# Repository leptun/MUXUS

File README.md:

# MUXUS
This repository contains the MUXUS project, a USB 2.0 switch with 4 inputs (3xB + 1C_PD) and 4 outputs (3xA + STM32)

The project is split into multiple logical parts, all interconected on a PCB.
1. Upstream USB ports
2. USB mux
3. USB hub
4. Downstream USB ports
5. STM32 microcontroller
6. USB PD sink
7. STM32 programming
8. 3.3V rail Buck converter

## 1. Upstream USB ports
There are 4 upstream capable USB ports (UFP1-UFP4): 3x USB-B and 1xUSB-C

The USB-B ports (UFP2-4) are protected by `USBLC6-2SC6` ICs (VBUS, D+/-).

The USB-C port (UFP1) is protected by a `USBLC6-4SC6` IC (VBUS, D+/-, CC1/2).

## 2. USB mux
All Upstream facing ports (UFP) are connected to the USB mux IC (`TS3USBCA420RSVR`).
The mux output is connected to an internal usb bus called IFP (inner facing port).
Even though this IC is designed to multiplex SBU pins on USB-C ports, its bandwidth is high enough for USB 2.0 signals.
This IC is connected to the MCU via a 400KHz I2C bus. All control is done via I2C.

## 3. USB hub
The IFP bus is split into multiple downstream ports (DFP1-DFP4) using a USB 2.0 HS hub (`USB2504A-JT`).
The hub has an I2C interface as well and it is connected to the MCU via the same 400KHz I2C bus.
Most of the control is done via the I2C bus, but there are also a few extra pins required:
- HUB_RESET. It is an active low signal with an external pull-up resistor. It is needed because the I2C bus gets disabled by the hub when the Attach command is executed by the hub.
- IFP_VBUS. The MCU emulates the VBUS connection of the upstream ports since the MUX IC doesn't do that on its own.

Each DFP has a pair of status LEDs (green and amber):
- The green LED indicates if the device is connected and powered. It turns off when the device is suspended or when it is disconnected.
- The amber LED indicates a fault in the port. This seems to only happen when the VBUS is shorted to GND.

## 4. Downstream USB ports
There are 4 downstream capable ports (DFP1-4), however only 3 have connectors (DFP2-4).

DFP1 is connected directly to the mcu and, as a result, no power circuitry is required for this one.

DFP2-4 are usb-A ports. Each port is protected by `USBLC6-2SC6` ICs (VBUS, D+/-) and VBUS is switched using `AP2151W` ICs.

## 5. STM32 microcontroller
The MCU is a `STM32G441KBU6`.
There are a few reasons why this mcu was chosen, but the main restriction that made me choose this was the IC shortage.

The requirements for the mcu were as follows:
- Enough pins for controlling the board. A QFN32 IC was barely enough for this task. A 48 pin IC would have been much easier to use.
- 4 ADC inputs
- An I2C bus
- USB C PD capabilities
- Some kind of debug interface

Even though these requirements could have been fulfilled by much simpler MCUs, I chose this one as I wanted to learn how to use this MCU family.

## 6. USB PD sink
I wanted this hub to be fully featured, so I made sure that all downstream ports are capable of delivering the full USB 2.0 power specification.
As a result, 1.5A + whatever else consumes power on the board is required. The only method I could achieve this is by either using an external 5V power supply, or by using a USBC-PD capable charger. I chose the latter.
With USBC-PD, the board can communicate with the charger directly and request up to 3A at 5V. I configured it to only request 2A.
The UCPD stack provided by ST is surprisingly heavy, eating up ~70KB of flash. Luckily, it leaves enough flash for the rest of the code.

# 7. STM32 programming
The MCU can be programmed in multiple ways:
- The STDC14 connector is the main method I used. It has a SWD interface, SWO trace support and a UART interface to the programmer, making development extremely easy, especially for the STM32CubeMonitor-UCPD tool. Even though the connector is a bit more expensive than I'd like, it is a single connector debug interface that has everything I'd ever need and it is compatible with the STLINK-V3 programmmer. The connector Part number is `FTSH-107-01-L-DV-K-A`
- A pair of 2.54mm pin headers. The same signals are exposed just like in the STDC14 connector, but in a less pleasant pinout.
- USB DFU firmware upload. If the CYCLE/BOOT0 button is held pressed while the reset button is released, the board enters the system memory boot option, through which code can be uploaded. Due to the way the hub is controlled, resetting the mcu will keep the last mux connection active, so code can be flashed through the mux and hub. There is a small design issue however (more on that in the Known issues section).

# 8. 3.3V rail Buck converter
This buck converter (`AOZ1212AI`) powers all the 3.3V ICs.
It is waaaaay overkill for this project, but I already had the ICs and wanted to implement them.
A small LDO would have been much better suited and it might even have been more stable.

# Known issues
- rev1
  - The ICs are painful to solder. I shouldn't have chosen QFN packages. Lesson learned.
  - The clock circuitry for the hub is wrong. 32pF capacitors should have been used and there should also be a 1M resistor between the crystal leads.
  - The USB signal routing is *horrible*. I'm surprised it works at all. I should improve that aspect if I ever make another revision (:doubt:).
  - There is a pinout conflict between the UCPD dead battery signals and the system memory DFU bootloader. When entering the bootloader, the DBCC1 gets assigned as USART1_TX, disabling the dead battery signal. As a result, power gets cut. This issue can be avoided if the usb C cable is connected with one of the ends reversed, so it works only 50% of the time. There are two solutions for a future revision of the board: I could use a protection IC with integrated DB signals such as the one used in X-NUCLEO-USBPDM1, or I could just use an MCU which doesn't have this pinout conflict (such as STM32G0B1KET6N or similar).
  - The component placement could be better and the board could be smaller.

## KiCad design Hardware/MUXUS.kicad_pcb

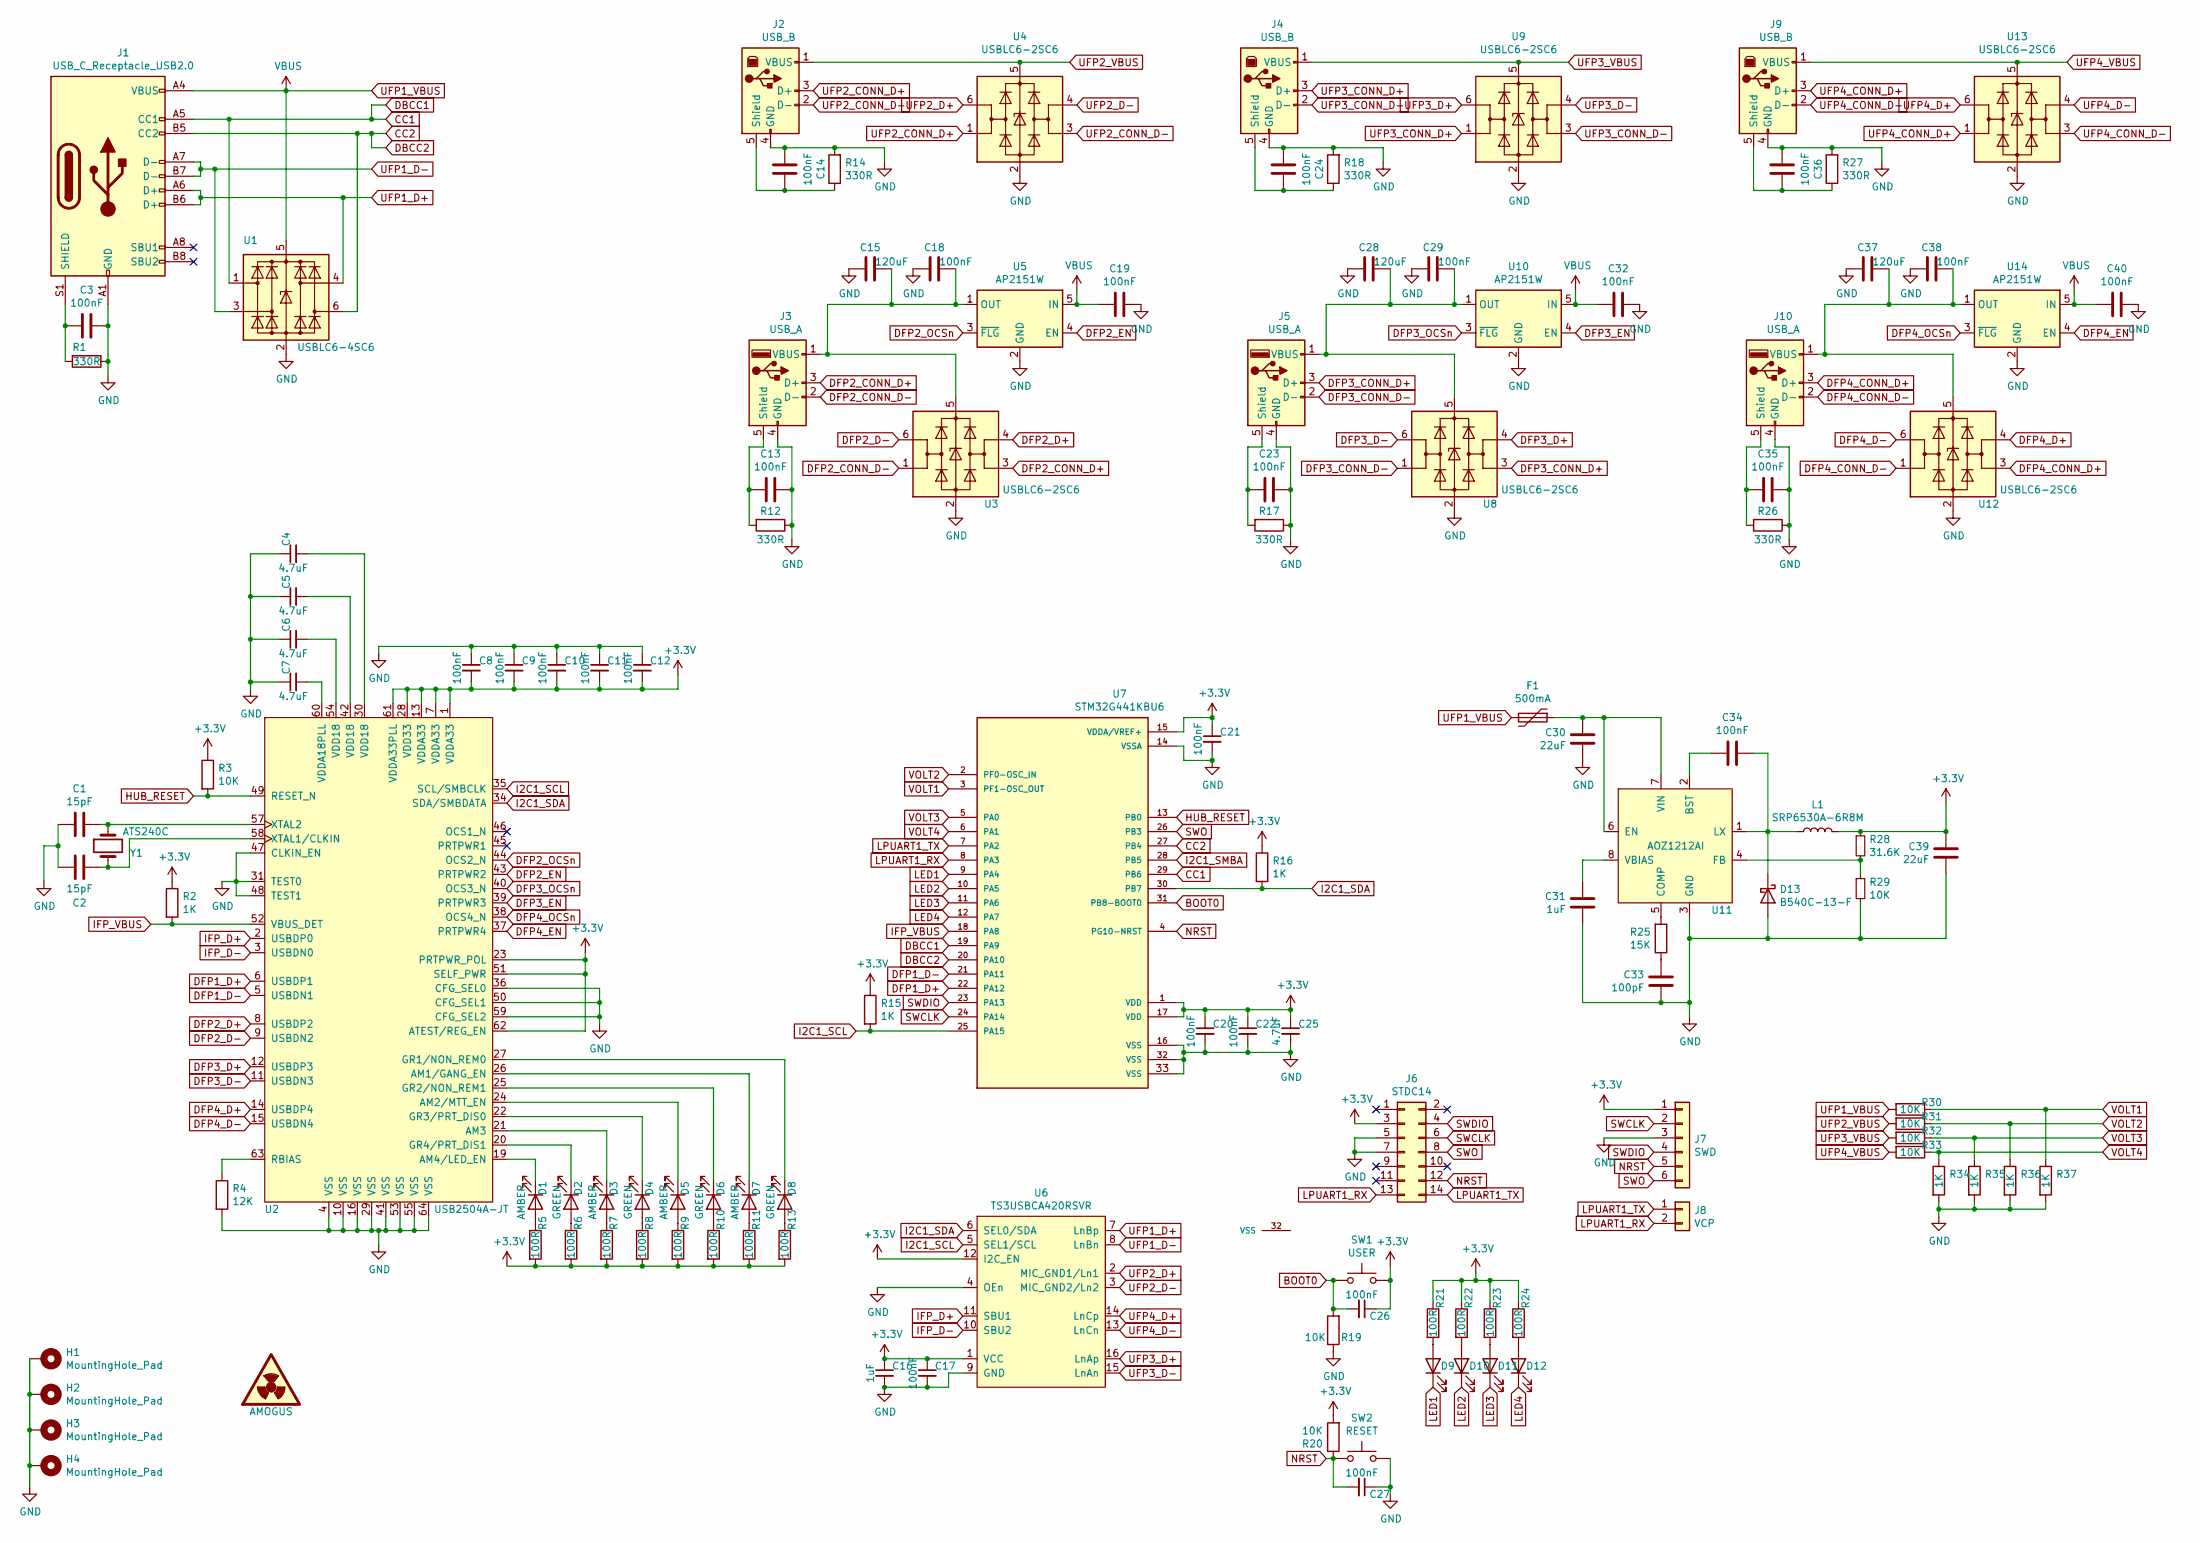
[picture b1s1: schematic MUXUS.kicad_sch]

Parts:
C1, C2: 15pF; C_0805_2012Metric
C3, C8, C9, C10, C11, C12, C13, C14, C17, C18, C19, C20, C21, C22, C23, C24, C26, C27, C29, C32, C34, C35, C36, C38, C40: 100nF; C_0805_2012Metric
C4, C5, C6, C7, C25: 4.7uF; C_1206_3216Metric
C15, C28, C37: 120uF; C_Radial_D6.3mm_H11.0mm_P2.50mm
C16, C31: 1uF; C_0805_2012Metric
C30, C39: 22uF; C_1210_3225Metric
C33: 100pF; C_0805_2012Metric
D1, D3, D5, D7: AMBER; LED_1206_3216Metric
D2, D4, D6, D8: GREEN; LED_1206_3216Metric
D9, D10, D11, D12: LED; LED_D5.0mm
D13: B540C-13-F; D_SMC
F1: 500mA; Fuse_1206_3216Metric
H1, H2, H3, H4: MountingHole_Pad; MountingHole_3.2mm_M3_Pad_Via
J1: USB_C_Receptacle_USB2.0; USB4110-GF-A
J2, J4, J9: USB_B; 67068-9000
J3, J5, J10: USB_A; 67643-0910
J6: STDC14; FTSH-107-01-L-DV-K-A
J7: SWD; PinHeader_1x06_P2.54mm_Vertical
J8: VCP; PinHeader_1x02_P2.54mm_Vertical
L1: SRP6530A-6R8M
R1, R12, R14, R17, R18, R26, R27: 330R; R_0805_2012Metric
R2, R15, R16, R34, R35, R36, R37: 1K; R_1206_3216Metric
R3, R19, R20, R29, R30, R31, R32, R33: 10K; R_1206_3216Metric
R4: 12K; R_1206_3216Metric
R5, R6, R7, R8, R9, R10, R11, R13, R21, R22, R23, R24: 100R; R_0805_2012Metric
R25: 15K; R_1206_3216Metric
R28: 31.6K; R_1206_3216Metric
SW1: USER; SW_Push_1P1T_NO_6x6mm_H9.5mm
SW2: RESET; SW_Push_1P1T_NO_6x6mm_H9.5mm
SYM1: AMOGUS; SUS
U1: USBLC6-4SC6; SOT-23-6
U2: USB2504A-JT; LQFP-64_10x10mm_P0.5mm
U3, U4, U8, U9, U12, U13: USBLC6-2SC6; SOT-23-6
U5, U10, U14: AP2151W; SOT-23-5
U6: TS3USBCA420RSVR
U7: STM32G441KBU6; PARTREV 2
U11: AOZ1212AI; SO-8_3.9x4.9mm_P1.27mm
Y1: ATS240C

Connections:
+3V3: C8.2, C9.2, C10.2, C11.2, C12.2, C16.1, C17.1, C20.1, C21.1, C22.1, C25.1, C26.1, C39.2, J6.3, J7.1, L1.2, R2.1, R3.1, R5.2, R6.2, R7.2, R8.2, R9.2, R10.2, R11.2, R13.2, R15.1, R16.1, R20.2, R21.1, R22.1, R23.1, R24.1, R28.1, SW1.2, U2.1 (VDDA33), U2.7 (VDDA33), U2.13 (VDDA33), U2.23 (PRTPWR_POL), U2.28 (VDD33), U2.51 (SELF_PWR), U2.61 (VDDA33PLL), U2.62 (ATEST/REG_EN), U6.1 (VCC), U6.12 (I2C_EN), U7.1 (VDD), U7.15 (VDDA/VREF+), U7.17 (VDD)
BOOT0: C26.2, R19.2, SW1.1, U7.31 (PB8-BOOT0)
CC1: J1.A5 (CC1), U1.1 (I/O1), U7.19 (PA9), U7.29 (PB6)
CC2: J1.B5 (CC2), U1.6 (I/O4), U7.20 (PA10), U7.27 (PB4)
DFP1_D+: U2.6 (USBDP1), U7.22 (PA12)
DFP1_D-: U2.5 (USBDN1), U7.21 (PA11)
DFP2_CONN_D+: J3.3 (D+), U3.3 (I/O2)
DFP2_CONN_D-: J3.2 (D-), U3.1 (I/O1)
DFP2_D+: U2.8 (USBDP2), U3.4 (I/O2)
DFP2_D-: U2.9 (USBDN2), U3.6 (I/O1)
DFP2_EN: U2.43 (PRTPWR2), U5.4 (EN)
DFP2_OCSn: U2.44 (OCS2_N), U5.3 (~FLG)
DFP3_CONN_D+: J5.3 (D+), U8.3 (I/O2)
DFP3_CONN_D-: J5.2 (D-), U8.1 (I/O1)
DFP3_D+: U2.12 (USBDP3), U8.4 (I/O2)
DFP3_D-: U2.11 (USBDN3), U8.6 (I/O1)
DFP3_EN: U2.39 (PRTPWR3), U10.4 (EN)
DFP3_OCSn: U2.40 (OCS3_N), U10.3 (~FLG)
DFP4_CONN_D+: J10.3 (D+), U12.3 (I/O2)
DFP4_CONN_D-: J10.2 (D-), U12.1 (I/O1)
DFP4_D+: U2.14 (USBDP4), U12.4 (I/O2)
DFP4_D-: U2.15 (USBDN4), U12.6 (I/O1)
DFP4_EN: U2.37 (PRTPWR4), U14.4 (EN)
DFP4_OCSn: U2.38 (OCS4_N), U14.3 (~FLG)
GND: C1.2, C2.1, C3.1, C4.1, C5.1, C6.1, C7.1, C8.1, C9.1, C10.1, C11.1, C12.1, C13.1, C14.2, C15.2, C16.2, C17.2, C18.2, C19.1, C20.2, C21.2, C22.2, C23.1, C24.2, C25.2, C27.1, C28.2, C29.2, C30.1, C31.1, C32.1, C33.1, C35.1, C36.2, C37.2, C38.2, C39.1, C40.1, D13.2 (A), H1.1, H2.1, H3.1, H4.1, J1.A1 (GND), J1.A12 (GND), J1.B1 (GND), J1.B12 (GND), J2.4 (GND), J3.4 (GND), J4.4 (GND), J5.4 (GND), J6.5, J6.7, J7.3, J9.4 (GND), J10.4 (GND), R1.1, R4.2, R12.1, R14.2, R17.1, R18.2, R19.1, R26.1, R27.2, R29.2, R34.2, R35.2, R36.2, R37.2, SW2.2, U1.2 (GND), U2.4 (VSS), U2.10 (VSS), U2.16 (VSS), U2.29 (VSS), U2.31 (TEST0), U2.36 (CFG_SEL0), U2.41 (VSS), U2.47 (CLKIN_EN), U2.48 (TEST1), U2.50 (CFG_SEL1), U2.53 (VSS), U2.55 (VSS), U2.59 (CFG_SEL2), U2.64 (VSS), U3.2 (GND), U4.2 (GND), U5.2 (GND), U6.4 (OEn), U6.9 (GND), U7.14 (VSSA), U7.16 (VSS), U7.32 (VSS), U7.33 (VSS), U8.2 (GND), U9.2 (GND), U10.2 (GND), U11.3 (GND), U12.2 (GND), U13.2 (GND), U14.2 (GND)
HUB_RESET: R3.2, U2.49 (RESET_N), U7.13 (PB0)
I2C1_SCL: R15.2, U2.35 (SCL/SMBCLK), U6.5 (SEL1/SCL), U7.25 (PA15)
I2C1_SDA: R16.2, U2.34 (SDA/SMBDATA), U6.6 (SEL0/SDA), U7.30 (PB7)
I2C1_SMBA: U7.28 (PB5)
IFP_D+: U2.2 (USBDP0), U6.11 (SBU1)
IFP_D-: U2.3 (USBDN0), U6.10 (SBU2)
IFP_VBUS: R2.2, U2.52 (VBUS_DET), U7.18 (PA8)
LED1: D9.1 (K), U7.9 (PA4)
LED2: D10.1 (K), U7.10 (PA5)
LED3: D11.1 (K), U7.11 (PA6)
LED4: D12.1 (K), U7.12 (PA7)
LPUART1_RX: J6.13, J8.2, U7.8 (PA3)
LPUART1_TX: J6.14, J8.1, U7.7 (PA2)
NRST: C27.2, J6.12, J7.5, R20.1, SW2.1, U7.4 (PG10-NRST)
unnamed: C1.1, U2.57 (XTAL2), Y1.1
unnamed: C2.2, U2.58 (XTAL1/CLKIN), Y1.2
unnamed: C3.2, J1.S1 (SHIELD), R1.2
unnamed: C4.2, U2.30 (VDD18)
unnamed: C5.2, U2.42 (VDD18)
unnamed: C6.2, U2.54 (VDD18)
unnamed: C7.2, U2.60 (VDDA18PLL)
unnamed: C13.2, J3.5 (Shield), R12.2
unnamed: C14.1, J2.5 (Shield), R14.1
unnamed: C15.1, C18.1, J3.1 (VBUS), U3.5 (VBUS), U5.1 (OUT)
unnamed: C23.2, J5.5 (Shield), R17.2
unnamed: C24.1, J4.5 (Shield), R18.1
unnamed: C28.1, C29.1, J5.1 (VBUS), U8.5 (VBUS), U10.1 (OUT)
unnamed: C30.2, F1.1, U11.6 (EN), U11.7 (VIN)
unnamed: C31.2, U11.8 (VBIAS)
unnamed: C33.2, R25.1
unnamed: C34.1, U11.2 (BST)
unnamed: C34.2, D13.1 (K), L1.1, U11.1 (LX)
unnamed: C35.2, J10.5 (Shield), R26.2
unnamed: C36.1, J9.5 (Shield), R27.1
unnamed: C37.1, C38.1, J10.1 (VBUS), U12.5 (VBUS), U14.1 (OUT)
unnamed: D1.1 (K), U2.19 (AM4/LED_EN)
unnamed: D1.2 (A), R5.1
unnamed: D2.1 (K), U2.20 (GR4/PRT_DIS1)
unnamed: D2.2 (A), R6.1
unnamed: D3.1 (K), U2.21 (AM3)
unnamed: D3.2 (A), R7.1
unnamed: D4.1 (K), U2.22 (GR3/PRT_DIS0)
unnamed: D4.2 (A), R8.1
unnamed: D5.1 (K), U2.24 (AM2/MTT_EN)
unnamed: D5.2 (A), R9.1
unnamed: D6.1 (K), U2.25 (GR2/NON_REM1)
unnamed: D6.2 (A), R10.1
unnamed: D7.1 (K), U2.26 (AM1/GANG_EN)
unnamed: D7.2 (A), R11.1
unnamed: D8.1 (K), U2.27 (GR1/NON_REM0)
unnamed: D8.2 (A), R13.1
unnamed: D9.2 (A), R21.2
unnamed: D10.2 (A), R22.2
unnamed: D11.2 (A), R23.2
unnamed: D12.2 (A), R24.2
unnamed: R4.1, U2.63 (RBIAS)
unnamed: R25.2, U11.5 (COMP)
unnamed: R28.2, R29.1, U11.4 (FB)
SWCLK: J6.6, J7.2, U7.24 (PA14)
SWDIO: J6.4, J7.4, U7.23 (PA13)
SWO: J6.8, J7.6, U7.26 (PB3)
UFP1_D+: J1.A6 (D+), J1.B6 (D+), U1.4 (I/O3), U6.7 (LnBp)
UFP1_D-: J1.A7 (D-), J1.B7 (D-), U1.3 (I/O2), U6.8 (LnBn)
UFP1_VBUS: C19.2, C32.2, C40.2, F1.2, J1.A4 (VBUS), J1.A9 (VBUS), J1.B4 (VBUS), J1.B9 (VBUS), R30.2, U1.5 (VBUS), U5.5 (IN), U10.5 (IN), U14.5 (IN)
UFP2_CONN_D+: J2.3 (D+), U4.1 (I/O1)
UFP2_CONN_D-: J2.2 (D-), U4.3 (I/O2)
UFP2_D+: U4.6 (I/O1), U6.2 (MIC_GND1/Ln1)
UFP2_D-: U4.4 (I/O2), U6.3 (MIC_GND2/Ln2)
UFP2_VBUS: J2.1 (VBUS), R31.2, U4.5 (VBUS)
UFP3_CONN_D+: J4.3 (D+), U9.1 (I/O1)
UFP3_CONN_D-: J4.2 (D-), U9.3 (I/O2)
UFP3_D+: U6.16 (LnAp), U9.6 (I/O1)
UFP3_D-: U6.15 (LnAn), U9.4 (I/O2)
UFP3_VBUS: J4.1 (VBUS), R32.2, U9.5 (VBUS)
UFP4_CONN_D+: J9.3 (D+), U13.1 (I/O1)
UFP4_CONN_D-: J9.2 (D-), U13.3 (I/O2)
UFP4_D+: U6.14 (LnCp), U13.6 (I/O1)
UFP4_D-: U6.13 (LnCn), U13.4 (I/O2)
UFP4_VBUS: J9.1 (VBUS), R33.2, U13.5 (VBUS)
VOLT1: R30.1, R37.1, U7.3 (PF1-OSC_OUT)
VOLT2: R31.1, R36.1, U7.2 (PF0-OSC_IN)
VOLT3: R32.1, R35.1, U7.5 (PA0)
VOLT4: R33.1, R34.1, U7.6 (PA1)

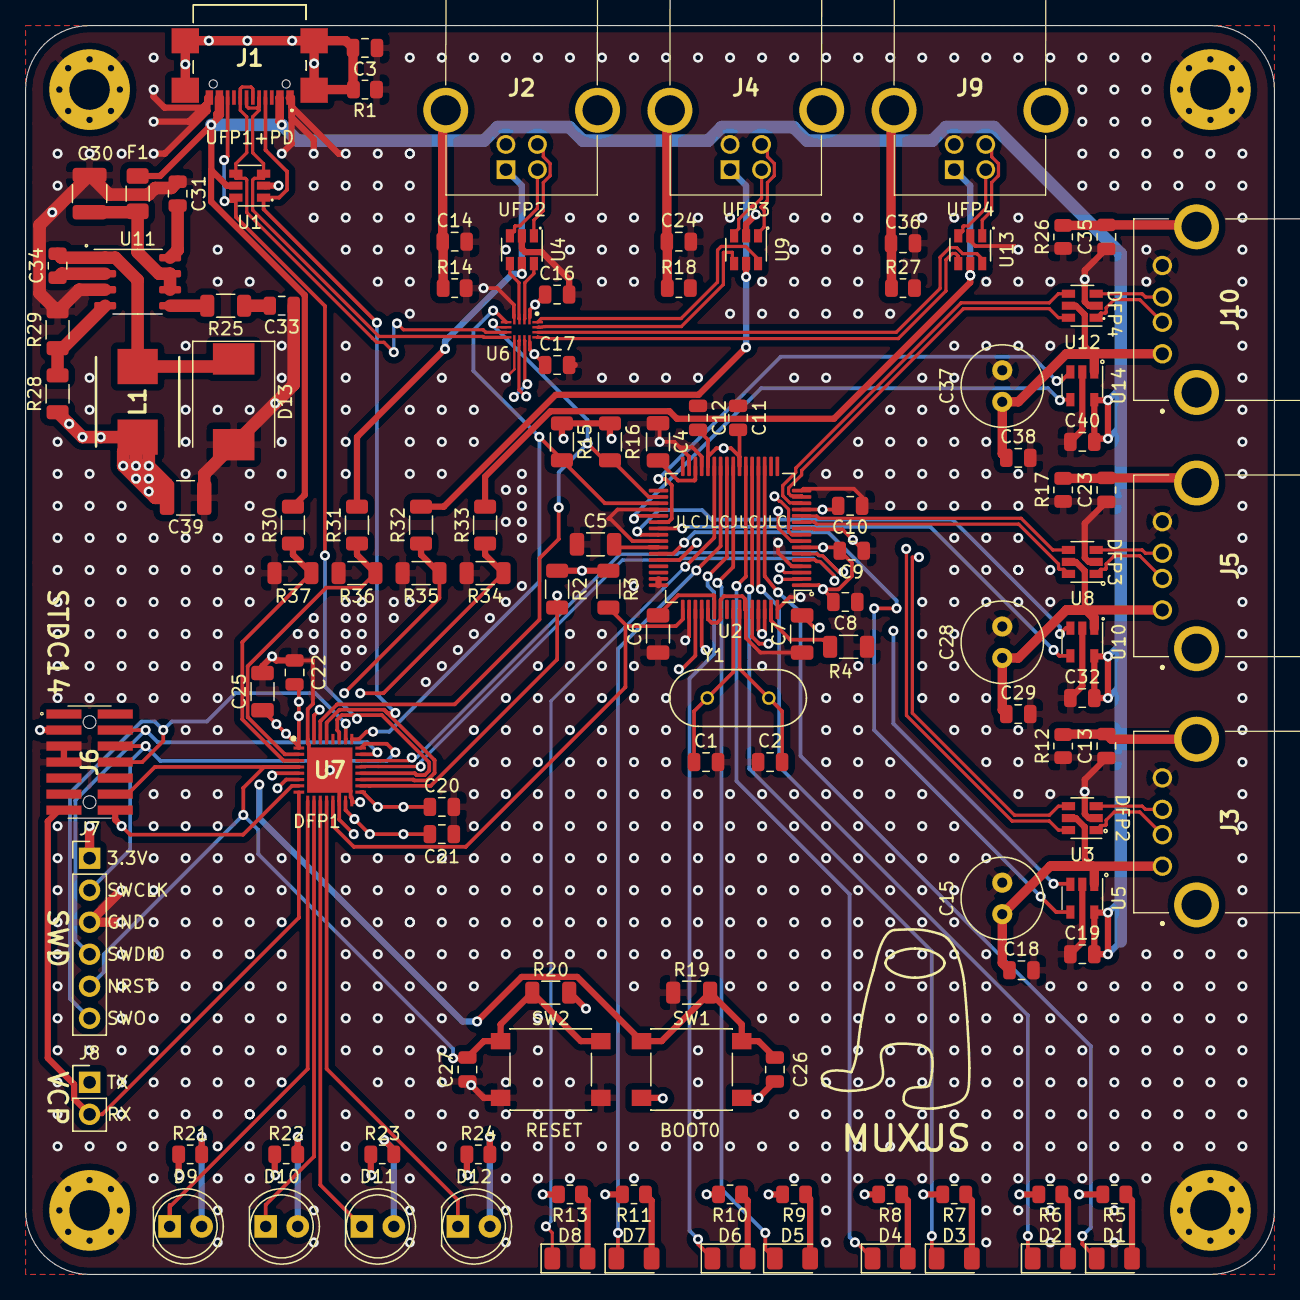
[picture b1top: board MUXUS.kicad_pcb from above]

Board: 4 copper layers, 99.1 x 99.1 mm, 124 parts (0 on the bottom side), 107 nets.

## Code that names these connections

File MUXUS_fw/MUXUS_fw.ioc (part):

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Mcu.Name=STM32G441KBUx
Mcu.Package=UFQFPN32
Mcu.UserName=STM32G441KBUx
PA0.GPIOParameters=GPIO_Label
PA0.GPIO_Label=VOLT3
PA0.Mode=IN1-Single-Ended
PA0.Signal=ADC1_IN1
PA1.GPIOParameters=GPIO_Label
PA1.GPIO_Label=VOLT4
PA1.Mode=IN2-Single-Ended
PA1.Signal=ADC1_IN2
PA10.Mode=EnableDeadBattery
PA10.Signal=UCPD1_DBCC2
PA11.Mode=Device
PA11.Signal=USB_DM
PA12.Mode=Device
PA12.Signal=USB_DP
PA13.Mode=Trace_Asynchronous_SW
PA13.Signal=SYS_JTMS-SWDIO
PA14.Mode=Trace_Asynchronous_SW
PA14.Signal=SYS_JTCK-SWCLK
PA15.Mode=I2C
PA15.Signal=I2C1_SCL
PA2.Mode=Asynchronous
PA2.Signal=LPUART1_TX
PA3.Mode=Asynchronous
PA3.Signal=LPUART1_RX
PA4.GPIOParameters=PinState,GPIO_Label,GPIO_ModeDefaultOutputPP
PA4.GPIO_Label=LED1
PA4.GPIO_ModeDefaultOutputPP=GPIO_MODE_OUTPUT_OD
PA4.PinState=GPIO_PIN_SET
PA4.Signal=GPIO_Output
PA5.GPIOParameters=PinState,GPIO_Label,GPIO_ModeDefaultOutputPP
PA5.GPIO_Label=LED2
PA5.GPIO_ModeDefaultOutputPP=GPIO_MODE_OUTPUT_OD
PA5.PinState=GPIO_PIN_SET
PA5.Signal=GPIO_Output
PA6.GPIOParameters=PinState,GPIO_Label,GPIO_ModeDefaultOutputPP
PA6.GPIO_Label=LED3
PA6.GPIO_ModeDefaultOutputPP=GPIO_MODE_OUTPUT_OD
PA6.PinState=GPIO_PIN_SET
PA6.Signal=GPIO_Output
PA7.GPIOParameters=PinState,GPIO_Label,GPIO_ModeDefaultOutputPP
PA7.GPIO_Label=LED4
PA7.GPIO_ModeDefaultOutputPP=GPIO_MODE_OUTPUT_OD
PA7.PinState=GPIO_PIN_SET
PA7.Signal=GPIO_Output
PA8.GPIOParameters=PinState,GPIO_Label,GPIO_ModeDefaultOutputPP
PA8.GPIO_Label=IFP_VBUS
PA8.GPIO_ModeDefaultOutputPP=GPIO_MODE_OUTPUT_OD
PA8.PinState=GPIO_PIN_SET
PA8.Signal=GPIO_Output
PA9.Mode=EnableDeadBattery
PA9.Signal=UCPD1_DBCC1
PB0.GPIOParameters=PinState,GPIO_Label,GPIO_ModeDefaultOutputPP
PB0.GPIO_Label=HUB_RESET
PB0.GPIO_ModeDefaultOutputPP=GPIO_MODE_OUTPUT_OD
PB0.PinState=GPIO_PIN_SET
PB0.Signal=GPIO_Output
PB3.Mode=Trace_Asynchronous_SW
PB3.Signal=SYS_JTDO-SWO
PB4.Mode=Sink_AllSignals
PB4.Signal=UCPD1_CC2
PB5.Signal=I2C1_SMBA
PB6.Mode=Sink_AllSignals
PB6.Signal=UCPD1_CC1
PB7.Mode=I2C
PB7.Signal=I2C1_SDA
PB8-BOOT0.GPIOParameters=GPIO_Label
PB8-BOOT0.GPIO_Label=BOOT0
PB8-BOOT0.Signal=GPIO_Input
PF0-OSC_IN.GPIOParameters=GPIO_Label
PF0-OSC_IN.GPIO_Label=VOLT2
PF0-OSC_IN.Mode=IN10-Single-Ended
PF0-OSC_IN.Signal=ADC1_IN10
PF1-OSC_OUT.GPIOParameters=GPIO_Label
PF1-OSC_OUT.GPIO_Label=VOLT1
PF1-OSC_OUT.Mode=IN10-Single-Ended
PF1-OSC_OUT.Signal=ADC2_IN10
PG10-NRST.GPIOParameters=GPIO_Label
PG10-NRST.GPIO_Label=NRST
PG10-NRST.Signal=GPIO_Input
RCC.HSE_VALUE=8000000
RCC.SYSCLKFreq_VALUE=170000000
RCC.SYSCLKSource=RCC_SYSCLKSOURCE_PLLCLK
board=custom

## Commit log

2021-09-12 Initial project
2021-09-12 First libs and project reorganization into HW and SW
2021-09-12 Checkpoint
2021-09-24 Checkpoint
    Supposed finalization of first prototype
2021-09-26 Prototype 1
2021-09-26 Mounting holes
2021-09-26 Basic board layout
2021-09-26 LED positioning
2021-09-26 More footprint positioning
2021-09-27 add older footprint from desktop
    todo: make combined libraries
2021-09-27 AMOGUS and USB C footprint update
2021-09-27 Component placement finished
2021-09-27 Rounded board edges
2021-09-27 Add trace widths
2021-09-27 Basic routing
2021-09-27 First PCB routing
2021-09-28 Add labels on silkscreen
2021-09-28 DEBUG connectors and VIAS
2021-09-28 JLCJLCJLCJLC
2021-09-28 Repair via gaps
2021-09-30 Remove datasheets
2021-10-01 UCPD test G474RE
2021-10-01 Measure UFP1_VBUS as well for the UCPD stack
2021-10-02 Updated STM32G441KBU6
2021-10-03 Repaired routing and fixed some 3d models
2021-10-03 Include solidworks model as well
2021-10-03 USB, mux and 3d models update
2021-10-03 Update UFP1 routing
2021-10-04 Tiny updates and first production test
2021-10-08 Filled all zones
2021-10-08 Add library submodule
2021-10-08 Updated submodule Hardware/leptunKicadLib.pretty
2021-10-08 Test new kicad
2021-10-08 AMOGUS
2021-10-08 Ignore backups
2021-10-08 USB2504A-JT
2021-10-08 TS3USBCA420RSVR
    .
2021-10-08 DX07S016JA1R1500
2021-10-09 FTSH-107-01-L-DV-K-A
2021-10-09 Fix FTSH-107-01-L-DV-K-A
2021-10-09 STM32G441KBU6
2021-10-09 ATS240C
2021-10-09 SRP6530A-6R8M
2021-10-09 67643-0910
2021-10-09 67068-9000
2021-10-09 AOZ1212AI
2021-10-09 AP2151W
2021-10-09 DTSM-61N-V-T_R
2021-10-09 Remove old stuff and backups
2021-10-09 Regenerate output
2021-10-09 Revision 1 + update output
2021-10-15 Remove old project file
2021-10-18 Fix VCP and SWD silkscreen orientation
2021-10-24 Regenerate project output
2021-11-11 Remove build from branch
2021-11-11 Ignore project output
2021-11-13 Functional-ish rev1
2021-11-13 stm32_libs
2021-11-13 Upstream cycle test
2021-11-15 Plastic case R1.1
2021-11-15 Ignore stupid file
2021-11-15 .no_init section
2021-11-15 Change PDO to 2.0A
2021-11-15 basic bootapp for system memory
2021-11-15 Add delay on main task startup. It helps with firmware upload reset cnt
2021-11-16 Updated libs
2021-11-16 Update gitignore
2021-11-16 Update libs
2021-11-17 Remove the G474RE UCPD test
2021-11-17 Create LICENSE
2023-08-23 rev2 dump
2024-03-23 Update to newer cubemx package
2024-03-23 Switch to usb msc
2024-03-23 Enable CRS on usb
2024-03-23 Make muxus appear without any media
2024-03-23 Add bowser bios workaround for getting it unstuck
